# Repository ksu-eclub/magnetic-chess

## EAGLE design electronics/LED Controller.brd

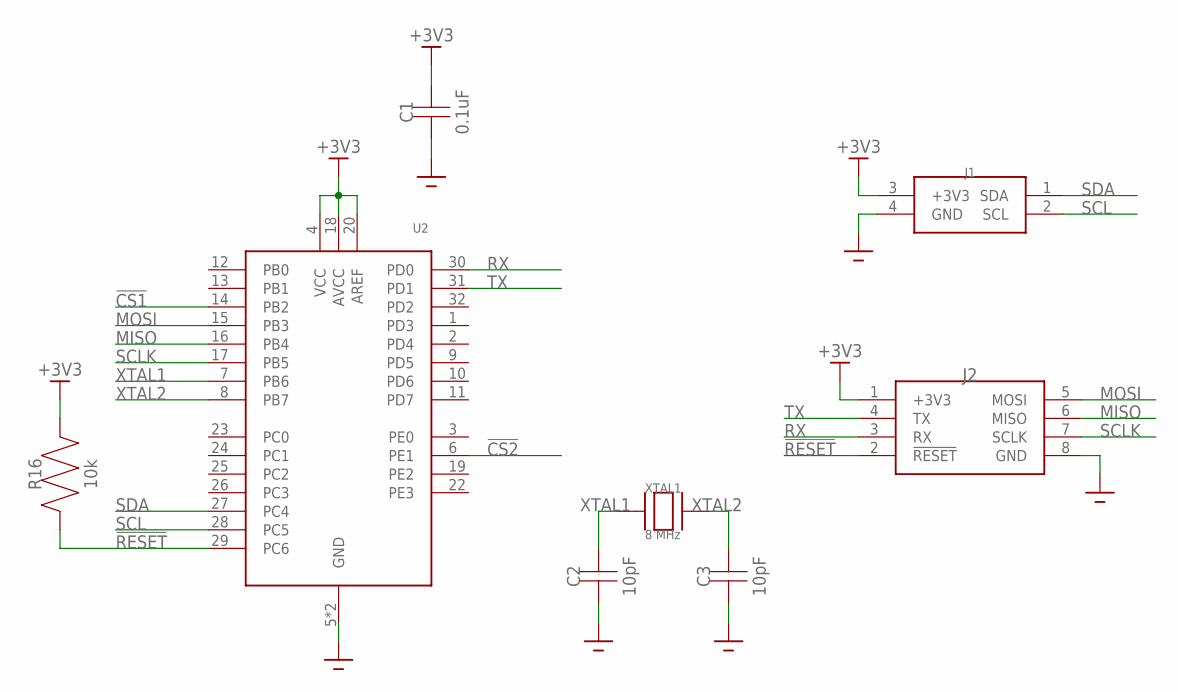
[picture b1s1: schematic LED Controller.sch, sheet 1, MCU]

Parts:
C1: 0.1uF; 0805
C2, C3: 10pF; 0805
J1: 1-770968-0
J2: DF1BZ-8DP-2.5DSA
R16: 10k; 0805
U2: ATMEGA328PB32-TQFP; ATMEGA328PB
XTAL1: 8 MHz; XRCGB

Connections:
!CS1: U2.14 (PB2); also elsewhere on the board
!CS2: U2.6 (PE1); also elsewhere on the board
!RESET: J2.2 (!RESET), R16.P$1, U2.29 (PC6)
+3V3: C1.P$2, J1.3 (+3V3), J2.1 (+3V3), R16.P$2, U2.4 (VCC), U2.18 (AVCC), U2.20 (AREF); also elsewhere on the board
GND: C1.P$1, C2.P$1, C3.P$1, J1.4 (GND), J2.8 (GND), U2.5 (GND), U2.21 (GND); also elsewhere on the board
MISO: J2.6 (MISO), U2.16 (PB4); also elsewhere on the board
MOSI: J2.5 (MOSI), U2.15 (PB3); also elsewhere on the board
RX: J2.3 (RX), U2.30 (PD0)
SCL: J1.2 (SCL), U2.28 (PC5)
SCLK: J2.7 (SCLK), U2.17 (PB5); also elsewhere on the board
SDA: J1.1 (SDA), U2.27 (PC4)
TX: J2.4 (TX), U2.31 (PD1)
XTAL1: C2.P$2, U2.7 (PB6), XTAL1.1, XTAL1.3
XTAL2: C3.P$2, U2.8 (PB7), XTAL1.2, XTAL1.4

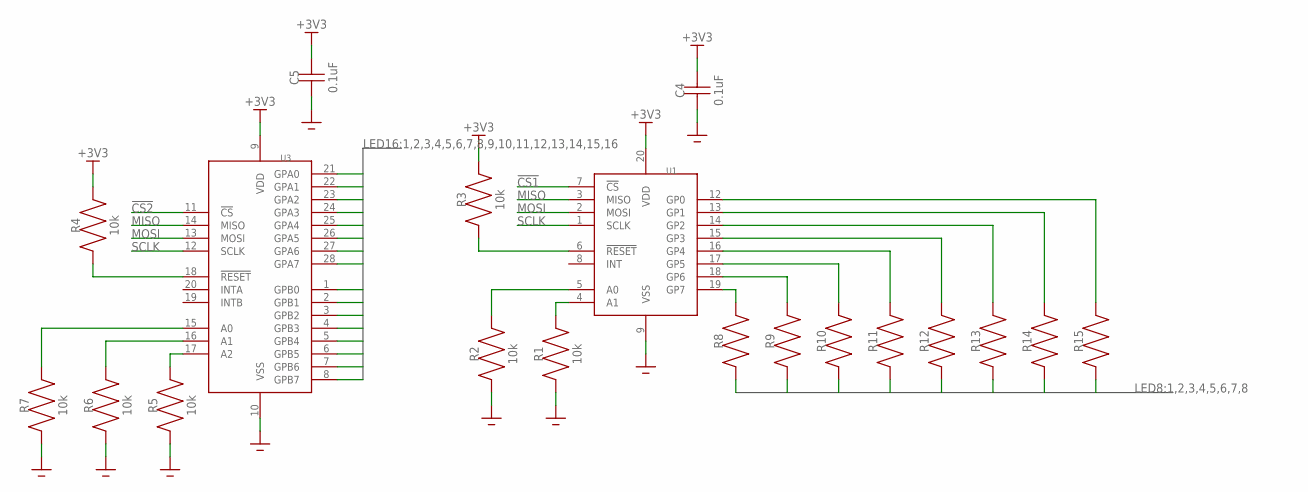
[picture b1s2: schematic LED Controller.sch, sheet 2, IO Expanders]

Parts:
C4, C5: 0.1uF; 0805
R1, R2, R3, R4, R5, R6, R7: 10k; 0805
R8, R9, R10, R11, R12, R13, R14, R15: RESISTOR0805; 0805
U1: MCP23S08-E/SO
U3: MCP23S17T-E/SO

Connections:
1: U3.21 (GPA0); also elsewhere on the board
2: U3.22 (GPA1); also elsewhere on the board
3: U3.23 (GPA2); also elsewhere on the board
4: U3.24 (GPA3); also elsewhere on the board
5: U3.25 (GPA4); also elsewhere on the board
6: U3.26 (GPA5); also elsewhere on the board
7: U3.27 (GPA6); also elsewhere on the board
8: U3.28 (GPA7); also elsewhere on the board
9: U3.1 (GPB0); also elsewhere on the board
10: U3.2 (GPB1); also elsewhere on the board
11: U3.3 (GPB2); also elsewhere on the board
12: U3.4 (GPB3); also elsewhere on the board
13: U3.5 (GPB4); also elsewhere on the board
14: U3.6 (GPB5); also elsewhere on the board
15: U3.7 (GPB6); also elsewhere on the board
16: U3.8 (GPB7); also elsewhere on the board
!CS1: U1.7 (!CS); also elsewhere on the board
!CS2: U3.11 (!CS); also elsewhere on the board
+3V3: C4.P$2, C5.P$2, R3.P$2, R4.P$2, U1.20 (VDD), U3.9 (VDD); also elsewhere on the board
A: R15.P$1; also elsewhere on the board
B: R14.P$1; also elsewhere on the board
C: R13.P$1; also elsewhere on the board
D: R12.P$1; also elsewhere on the board
E: R11.P$1; also elsewhere on the board
F: R10.P$1; also elsewhere on the board
G: R9.P$1; also elsewhere on the board
GND: C4.P$1, C5.P$1, R1.P$1, R2.P$1, R5.P$1, R6.P$1, R7.P$1, U1.9 (VSS), U3.10 (VSS); also elsewhere on the board
H: R8.P$1; also elsewhere on the board
MISO: U1.3 (MISO), U3.14 (MISO); also elsewhere on the board
MOSI: U1.2 (MOSI), U3.13 (MOSI); also elsewhere on the board
unnamed: R1.P$2, U1.4 (A1)
unnamed: R2.P$2, U1.5 (A0)
unnamed: R3.P$1, U1.6 (!RESET)
unnamed: R4.P$1, U3.18 (!RESET)
unnamed: R5.P$2, U3.17 (A2)
unnamed: R6.P$2, U3.16 (A1)
unnamed: R7.P$2, U3.15 (A0)
unnamed: R8.P$2, U1.19 (GP7)
unnamed: R9.P$2, U1.18 (GP6)
unnamed: R10.P$2, U1.17 (GP5)
unnamed: R11.P$2, U1.16 (GP4)
unnamed: R12.P$2, U1.15 (GP3)
unnamed: R13.P$2, U1.14 (GP2)
unnamed: R14.P$2, U1.13 (GP1)
unnamed: R15.P$2, U1.12 (GP0)
SCLK: U1.1 (SCLK), U3.12 (SCLK); also elsewhere on the board

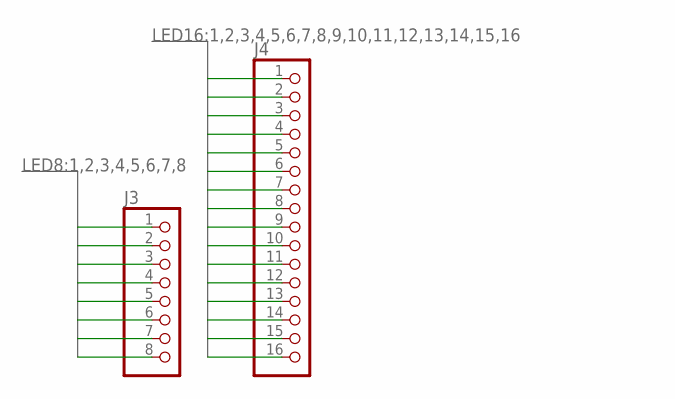
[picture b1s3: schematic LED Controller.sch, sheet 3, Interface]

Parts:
J3: LED8
J4: LED16

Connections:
1: J4.1; also elsewhere on the board
2: J4.2; also elsewhere on the board
3: J4.3; also elsewhere on the board
4: J4.4; also elsewhere on the board
5: J4.5; also elsewhere on the board
6: J4.6; also elsewhere on the board
7: J4.7; also elsewhere on the board
8: J4.8; also elsewhere on the board
9: J4.9; also elsewhere on the board
10: J4.10; also elsewhere on the board
11: J4.11; also elsewhere on the board
12: J4.12; also elsewhere on the board
13: J4.13; also elsewhere on the board
14: J4.14; also elsewhere on the board
15: J4.15; also elsewhere on the board
16: J4.16; also elsewhere on the board
A: J3.1; also elsewhere on the board
B: J3.2; also elsewhere on the board
C: J3.3; also elsewhere on the board
D: J3.4; also elsewhere on the board
E: J3.5; also elsewhere on the board
F: J3.6; also elsewhere on the board
G: J3.7; also elsewhere on the board
H: J3.8; also elsewhere on the board

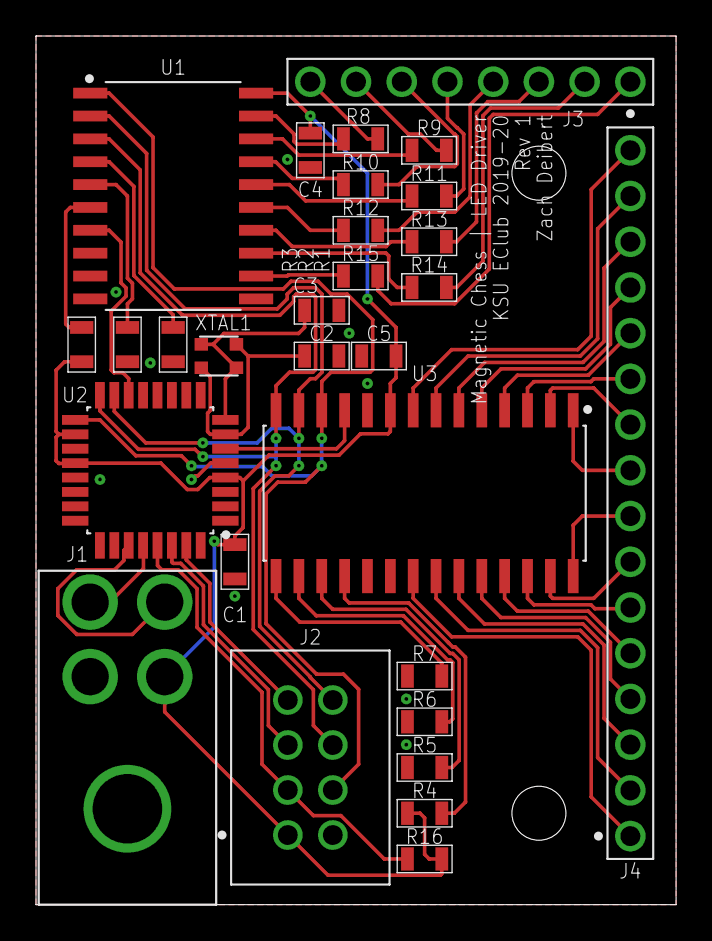
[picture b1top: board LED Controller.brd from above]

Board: 2 copper layers, 35.6 x 48.3 mm, 29 parts (0 on the bottom side), 53 nets.

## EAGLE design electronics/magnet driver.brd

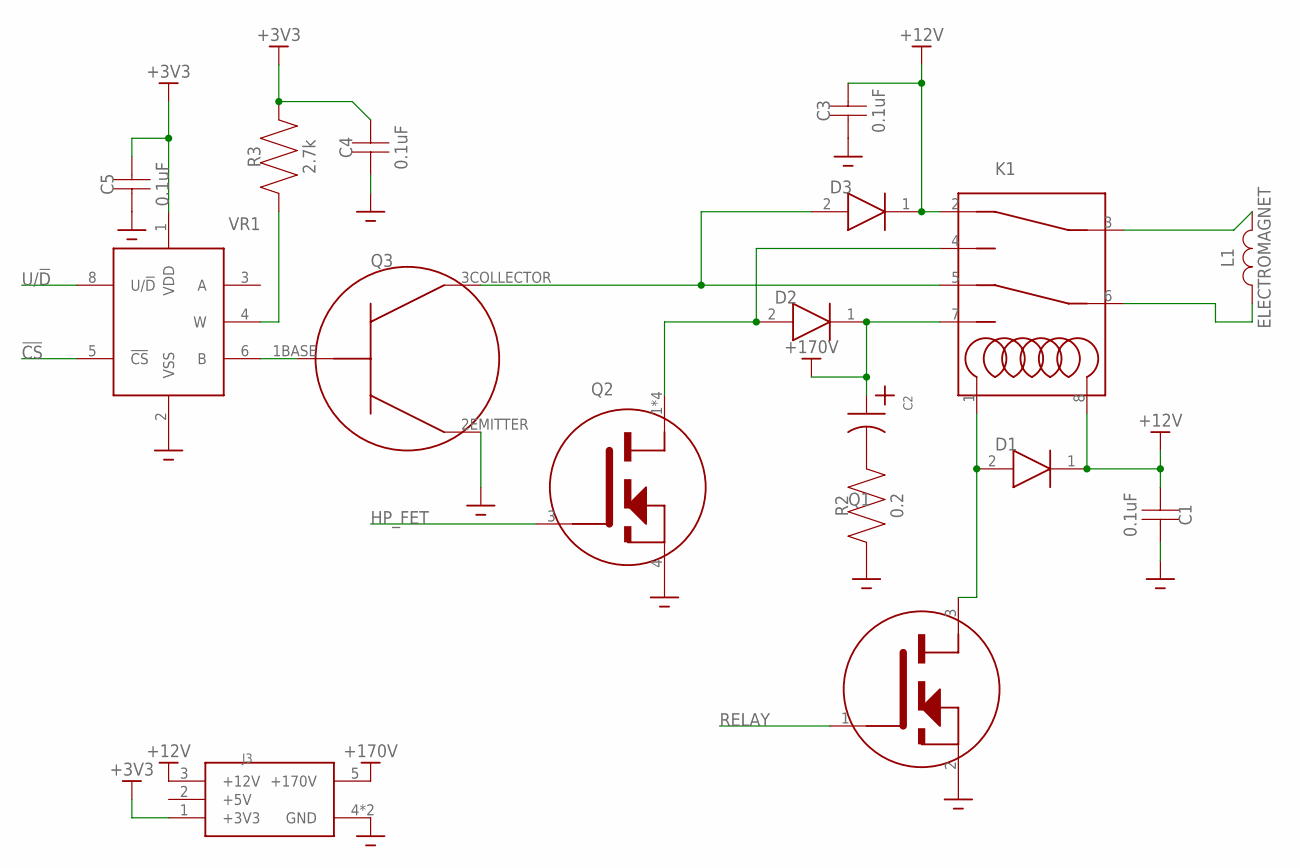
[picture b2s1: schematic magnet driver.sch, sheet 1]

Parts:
C1, C3, C4, C5: 0.1uF; 0805
C2: ESMQ351VSN102MA50S
D1, D2, D3: BAT54HT1GBAT54HT1G; SOD2512X110N
J3: 1-770969-0
K1: G2RL-2DC12
L1: ELECTROMAGNET
Q1: RK7002BMT116; SOT95P240X120-3N
Q2: DMN1019UVT-7DMN1019UVT-7; SOT95P280X100-6N
Q3: PMBT2222A,215PMBT2222A,215; SOT95P230X110-3N
R2: 0.2; 0805
R3: 2.7k; 0805
VR1: MCP4011-103E/MSMCP4011-103E/MS; SOP65P490X265-8N

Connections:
!CS: VR1.5 (!CS); also elsewhere on the board
+3V3: C4.P$2, C5.P$2, J3.1 (+3V3), R3.P$2, VR1.1 (VDD); also elsewhere on the board
+5V: J3.2 (+5V)
+12V: C1.P$1, C3.P$2, D1.1 (CATHODE(1)), D3.1 (CATHODE(1)), J3.3 (+12V), K1.2 (A1), K1.8 (COILOUT)
+170V: C2.+, D2.1 (CATHODE(1)), J3.5 (+170V), K1.7 (B2)
GND: C1.P$2, C3.P$1, C4.P$1, C5.P$1, J3.4 (GND), J3.6 (GND), Q1.2 (SOURCE(2)), Q2.4 (SOURCE(2)), Q3.2EMITTER (2E), R2.P$1, VR1.2 (VSS); also elsewhere on the board
HP_FET: Q2.3 (GATE(1)); also elsewhere on the board
unnamed: K1.3 (A), L1.-
unnamed: C2.-, R2.P$2
unnamed: D1.2 (ANODE(2)), K1.1 (COILIN), Q1.3 (DRAIN(3))
unnamed: K1.6 (B), L1.+
unnamed: Q3.1BASE (1B), VR1.6 (B)
unnamed: R3.P$1, VR1.4 (W)
unnamed: D3.2 (ANODE(2)), K1.5 (B1), Q3.3COLLECTOR (3C)
unnamed: D2.2 (ANODE(2)), K1.4 (A2), Q2.1 (DRAIN(3)), Q2.2 (DRAIN(3)), Q2.5 (DRAIN(3)), Q2.6 (DRAIN(3))
RELAY: Q1.1 (GATE(1)); also elsewhere on the board
U/!D: VR1.8 (U/!D); also elsewhere on the board

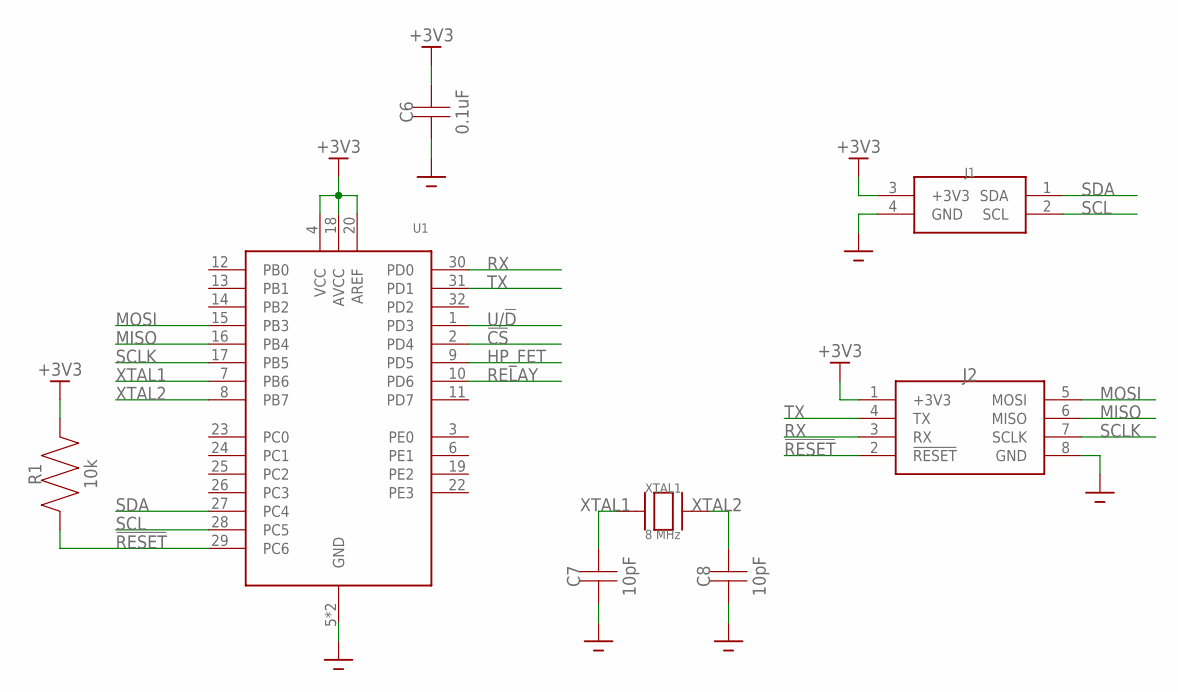
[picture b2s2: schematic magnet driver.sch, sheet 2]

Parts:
C6: 0.1uF; 0805
C7, C8: 10pF; 0805
J1: 1-770968-0
J2: DF1BZ-8DP-2.5DSA
R1: 10k; 0805
U1: ATMEGA328PB32-TQFP; ATMEGA328PB
XTAL1: 8 MHz; XRCGB

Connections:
!CS: U1.2 (PD4); also elsewhere on the board
!RESET: J2.2 (!RESET), R1.P$1, U1.29 (PC6)
+3V3: C6.P$2, J1.3 (+3V3), J2.1 (+3V3), R1.P$2, U1.4 (VCC), U1.18 (AVCC), U1.20 (AREF); also elsewhere on the board
GND: C6.P$1, C7.P$1, C8.P$1, J1.4 (GND), J2.8 (GND), U1.5 (GND), U1.21 (GND); also elsewhere on the board
HP_FET: U1.9 (PD5); also elsewhere on the board
MISO: J2.6 (MISO), U1.16 (PB4)
MOSI: J2.5 (MOSI), U1.15 (PB3)
RELAY: U1.10 (PD6); also elsewhere on the board
RX: J2.3 (RX), U1.30 (PD0)
SCL: J1.2 (SCL), U1.28 (PC5)
SCLK: J2.7 (SCLK), U1.17 (PB5)
SDA: J1.1 (SDA), U1.27 (PC4)
TX: J2.4 (TX), U1.31 (PD1)
U/!D: U1.1 (PD3); also elsewhere on the board
XTAL1: C7.P$2, U1.7 (PB6), XTAL1.1, XTAL1.3
XTAL2: C8.P$2, U1.8 (PB7), XTAL1.2, XTAL1.4

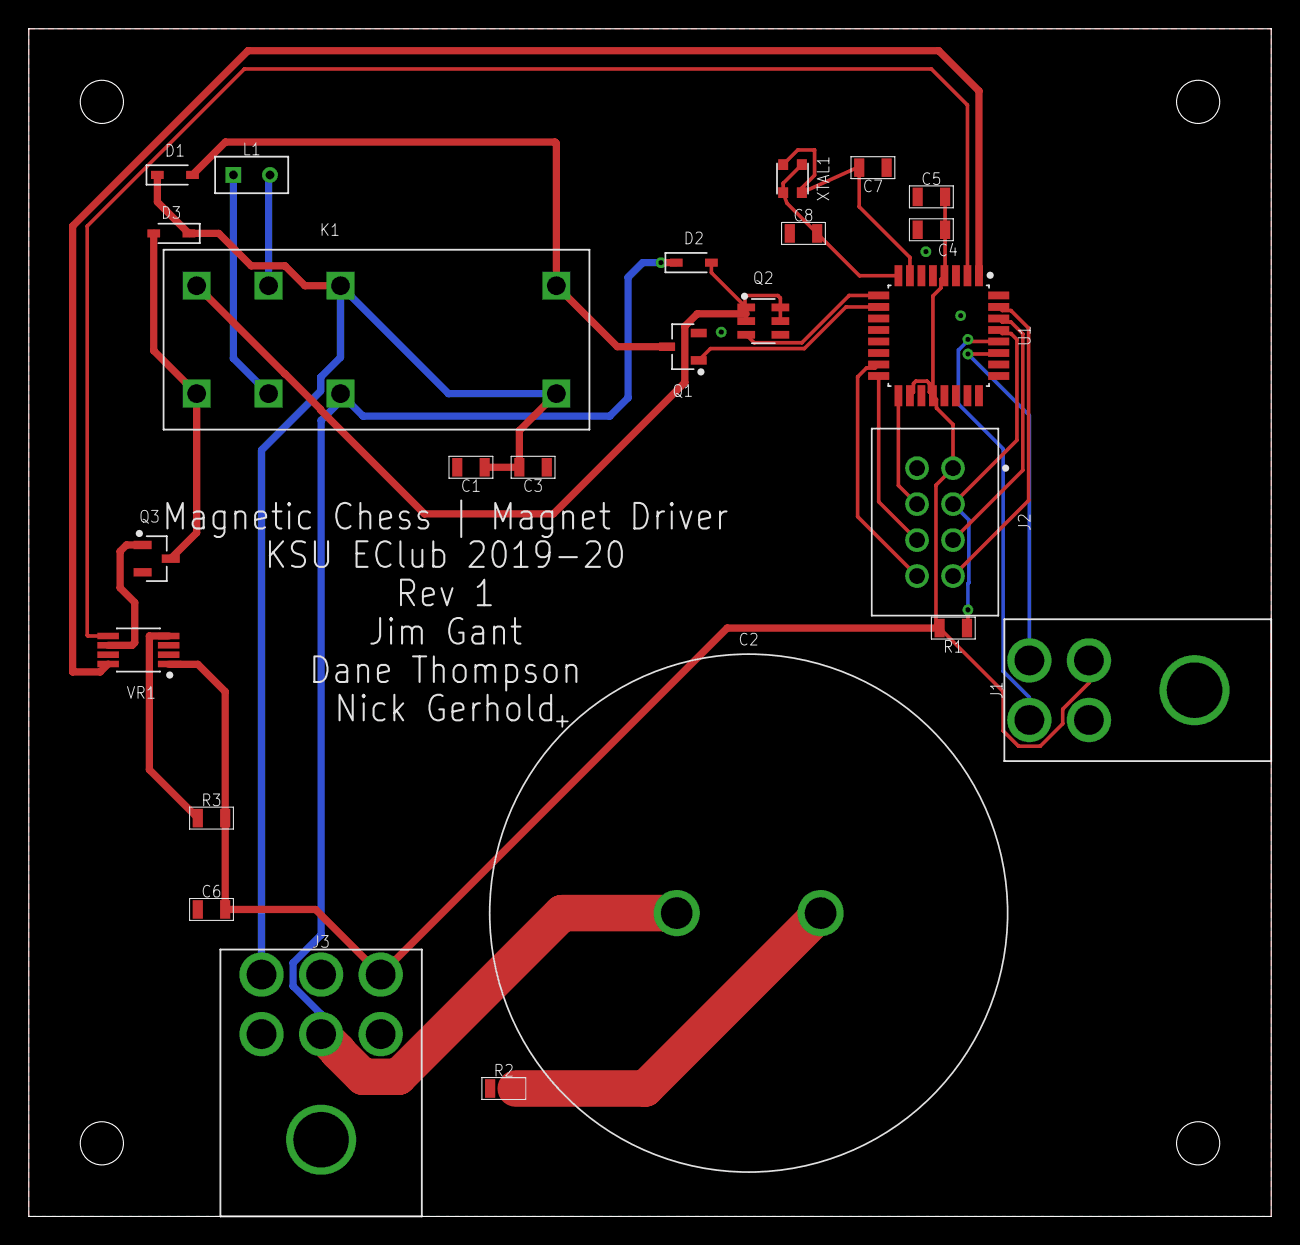
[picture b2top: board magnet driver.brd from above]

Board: 2 copper layers, 86.4 x 82.5 mm, 25 parts (0 on the bottom side), 26 nets.

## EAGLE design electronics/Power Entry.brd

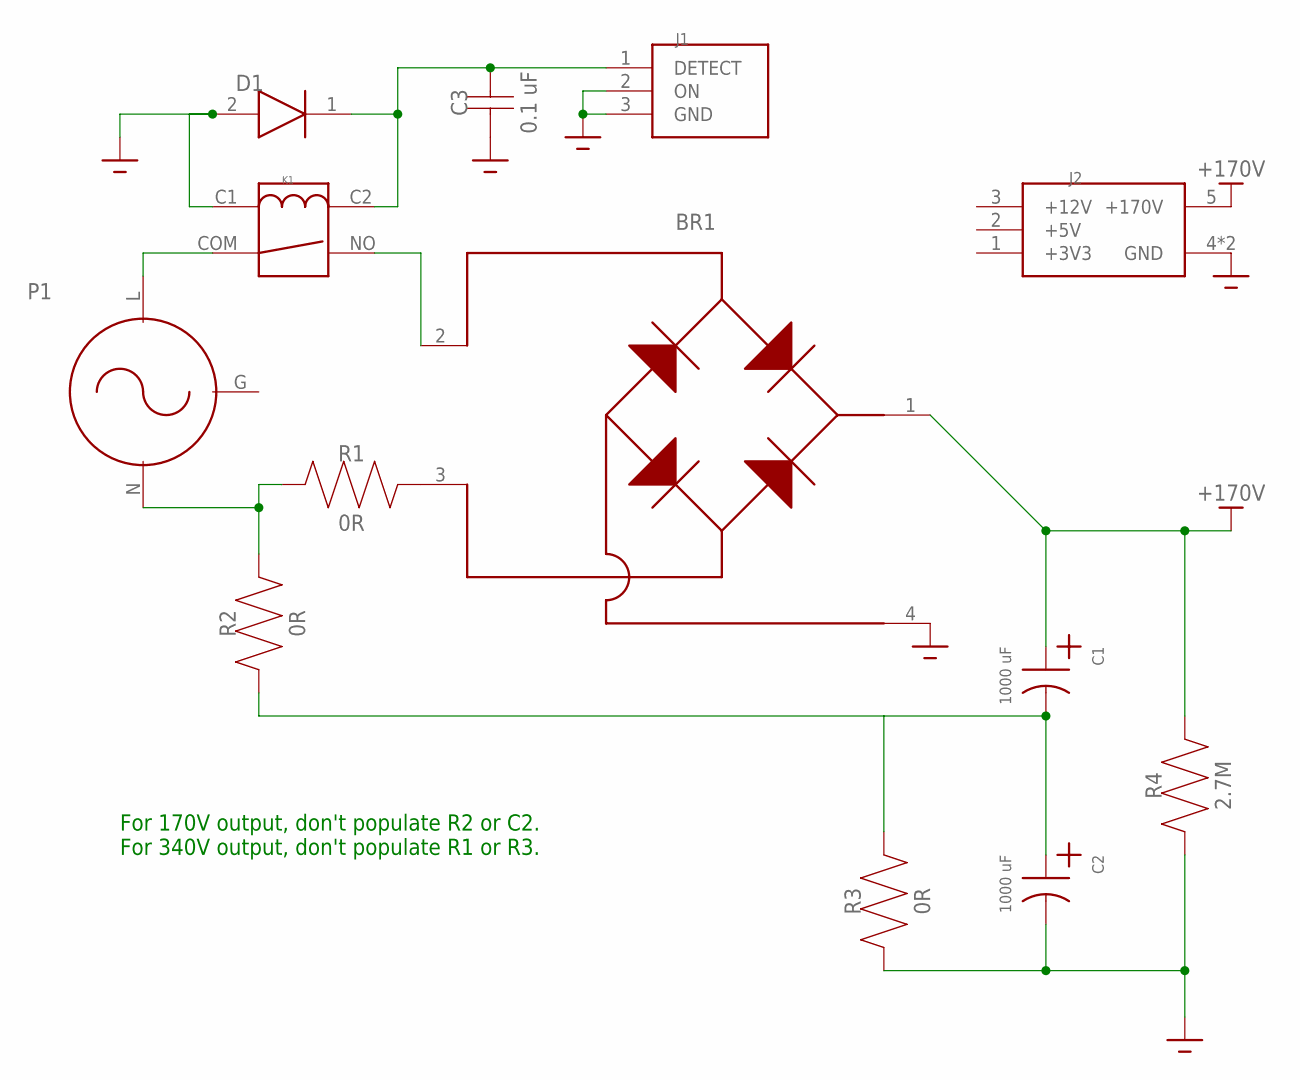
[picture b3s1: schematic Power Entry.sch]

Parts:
BR1: GBJ1004-BP
C1, C2: 1000 uF; ESMQ351VSN102MA50S
C3: 0.1 uF; 0805
D1: BAT54HT1GBAT54HT1G; SOD2512X110N
J1: 1-770967-0
J2: 1-770969-0
K1: ALQ3F12
P1: 703W-00/04
R1, R2, R3: 0R; 0805
R4: 2.7M; 0805

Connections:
+3V3: J2.1 (+3V3)
+5V: J2.2 (+5V)
+12V: J2.3 (+12V)
+170V: BR1.1 (POSITIVE_DC), C1.+, J2.5 (+170V), R4.P$2
GND: BR1.4 (NEGATIVE_DC), C2.-, C3.P$1, D1.2 (ANODE(2)), J1.2 (ON), J1.3 (GND), J2.4 (GND), J2.6 (GND), K1.C1, R3.P$1, R4.P$1
unnamed: BR1.3 (AC_IN2), R1.P$2
unnamed: P1.N (NEUTRAL), R1.P$1, R2.P$2
unnamed: C1.-, C2.+, R2.P$1, R3.P$2
unnamed: K1.COM (S1), P1.L (LIVE)
unnamed: BR1.2 (AC_IN1), K1.NO (S2)
unnamed: C3.P$2, D1.1 (CATHODE(1)), J1.1 (DETECT), K1.C2

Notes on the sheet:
For 170V output, don't populate R2 or C2. For 340V output, don't populate R1 or R3.

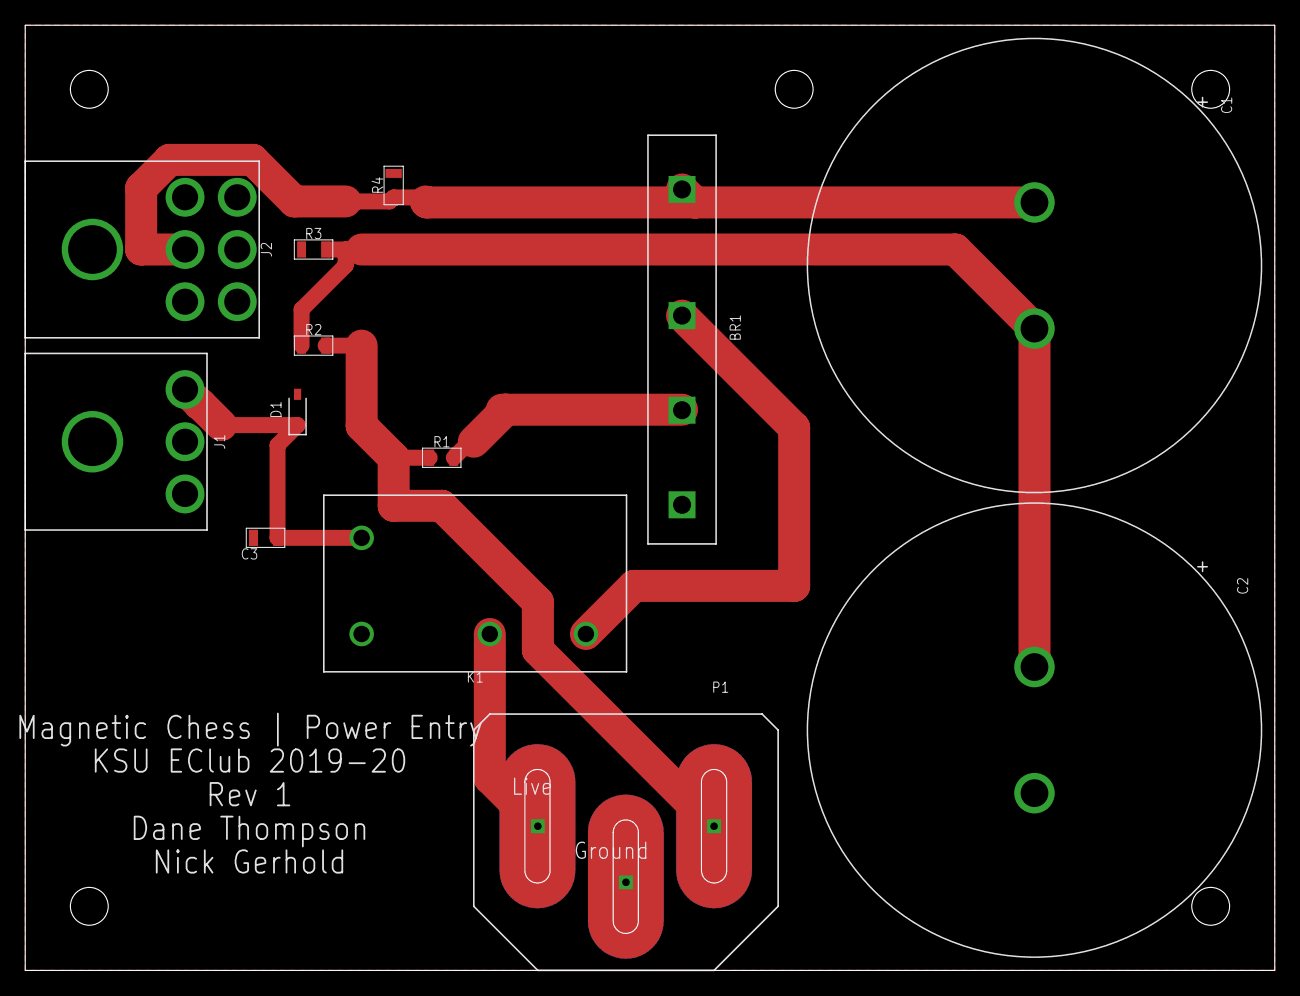
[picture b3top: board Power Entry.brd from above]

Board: 2 copper layers, 99.1 x 74.9 mm, 13 parts (0 on the bottom side), 8 nets.

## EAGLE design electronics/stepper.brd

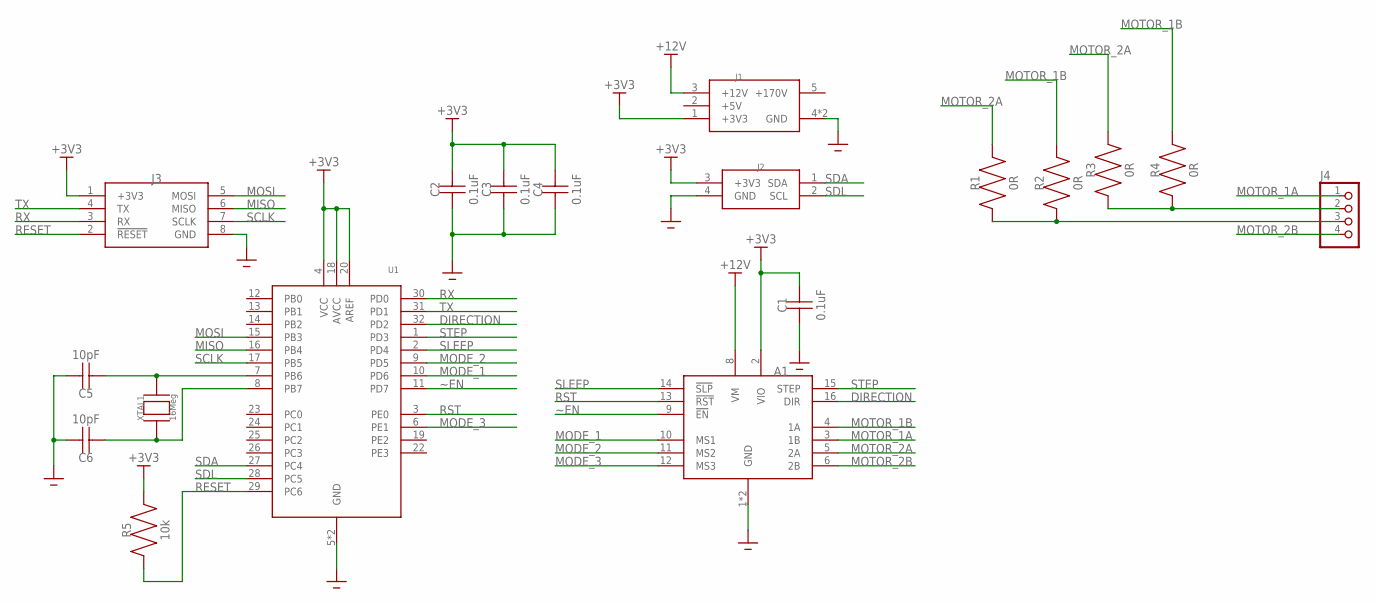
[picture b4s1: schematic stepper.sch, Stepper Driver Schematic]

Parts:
A1: STEPPER_DRIVER
C1, C2, C3, C4: 0.1uF; 0402
C5, C6: 10pF; 0402
J1: 1-770969-0
J2: 1-770968-0
J3: DF1BZ-8DP-2.5DSA
J4: S4B-XH-A
R1, R2, R3, R4: 0R; 0402
R5: 10k; 0402
U1: ATMEGA328PB32-TQFP; ATMEGA328PB
XTAL1: 16Meg; XRCGB

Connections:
+3V3: A1.2 (VIO), C1.2, C2.2, C3.2, C4.2, J1.1 (+3V3), J2.3 (+3V3), J3.1 (+3V3), R5.2, U1.4 (VCC), U1.18 (AVCC), U1.20 (AREF)
+5V: J1.2 (+5V)
+12V: A1.8 (VM), J1.3 (+12V)
+170V: J1.5 (+170V)
DIRECTION: A1.16 (DIR), U1.32 (PD2)
GND: A1.1 (GND), A1.7 (GND), C1.1, C2.1, C3.1, C4.1, C5.2, C6.2, J1.4 (GND), J1.6 (GND), J2.4 (GND), J3.8 (GND), U1.5 (GND), U1.21 (GND)
MISO: J3.6 (MISO), U1.16 (PB4)
MODE_1: A1.10 (MS1), U1.10 (PD6)
MODE_2: A1.11 (MS2), U1.9 (PD5)
MODE_3: A1.12 (MS3), U1.6 (PE1)
MOSI: J3.5 (MOSI), U1.15 (PB3)
MOTOR_1A: A1.3 (1B), J4.1
MOTOR_1B: A1.4 (1A), R2.2, R4.2
MOTOR_2A: A1.5 (2A), R1.2, R3.2
MOTOR_2B: A1.6 (2B), J4.4
unnamed: C5.1, U1.7 (PB6), XTAL1.2, XTAL1.4
unnamed: C6.1, U1.8 (PB7), XTAL1.1, XTAL1.3
unnamed: J4.2, R3.1, R4.1
unnamed: J4.3, R1.1, R2.1
RESET: J3.2 (!RESET), R5.1, U1.29 (PC6)
RST: A1.13 (!RST), U1.3 (PE0)
RX: J3.3 (RX), U1.30 (PD0)
SCLK: J3.7 (SCLK), U1.17 (PB5)
SDA: J2.1 (SDA), U1.27 (PC4)
SDL: J2.2 (SCL), U1.28 (PC5)
SLEEP: A1.14 (!SLP), U1.2 (PD4)
STEP: A1.15 (STEP), U1.1 (PD3)
TX: J3.4 (TX), U1.31 (PD1)
~EN: A1.9 (!EN), U1.11 (PD7)

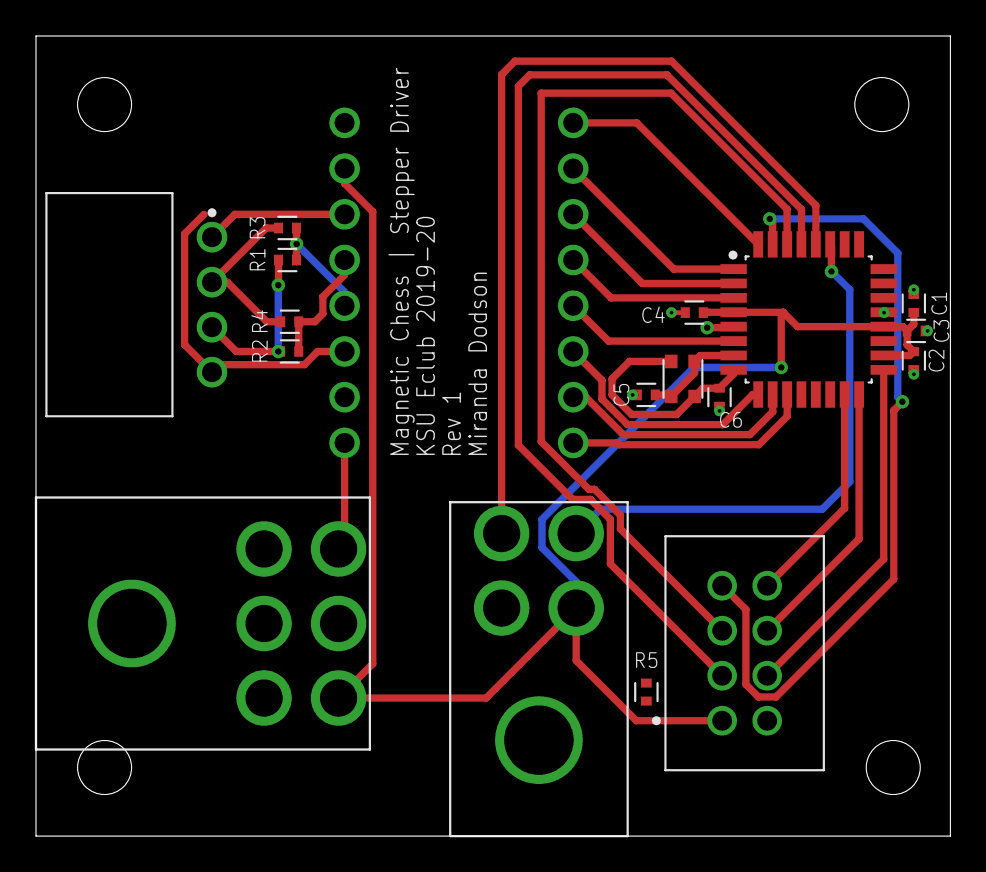
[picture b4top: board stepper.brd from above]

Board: 2 copper layers, 50.8 x 44.5 mm, 18 parts (1 on the bottom side), 27 nets.

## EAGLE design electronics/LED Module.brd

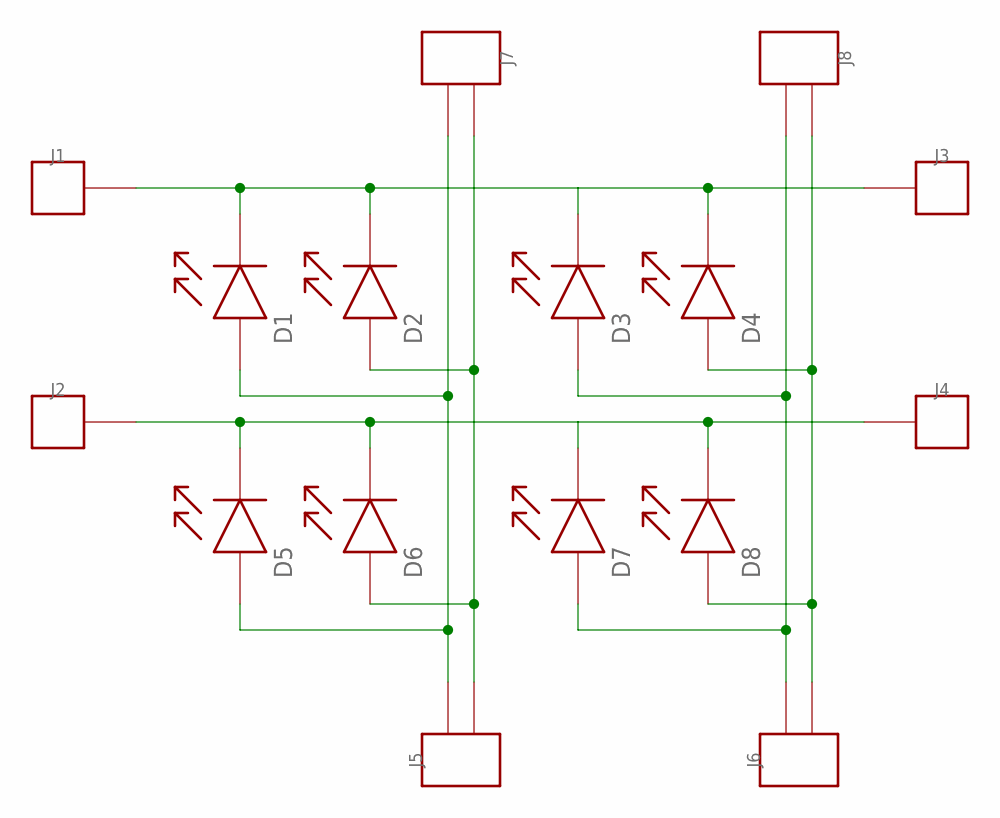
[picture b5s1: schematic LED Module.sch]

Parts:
D1, D2, D3, D4, D5, D6, D7, D8: LED; 0805-POL
J1, J2, J3, J4: LED_JUMPER_1
J5, J6, J7, J8: LED_JUMPER_2

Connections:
unnamed: D1.+ (K), D2.+ (K), D3.+ (K), D4.+ (K), J1.1, J3.1
unnamed: D1.COM (A), D5.COM (A), J5.1, J7.2
unnamed: D2.COM (A), D6.COM (A), J5.2, J7.1
unnamed: D5.+ (K), D6.+ (K), D7.+ (K), D8.+ (K), J2.1, J4.1
unnamed: D3.COM (A), D7.COM (A), J6.1, J8.2
unnamed: D4.COM (A), D8.COM (A), J6.2, J8.1

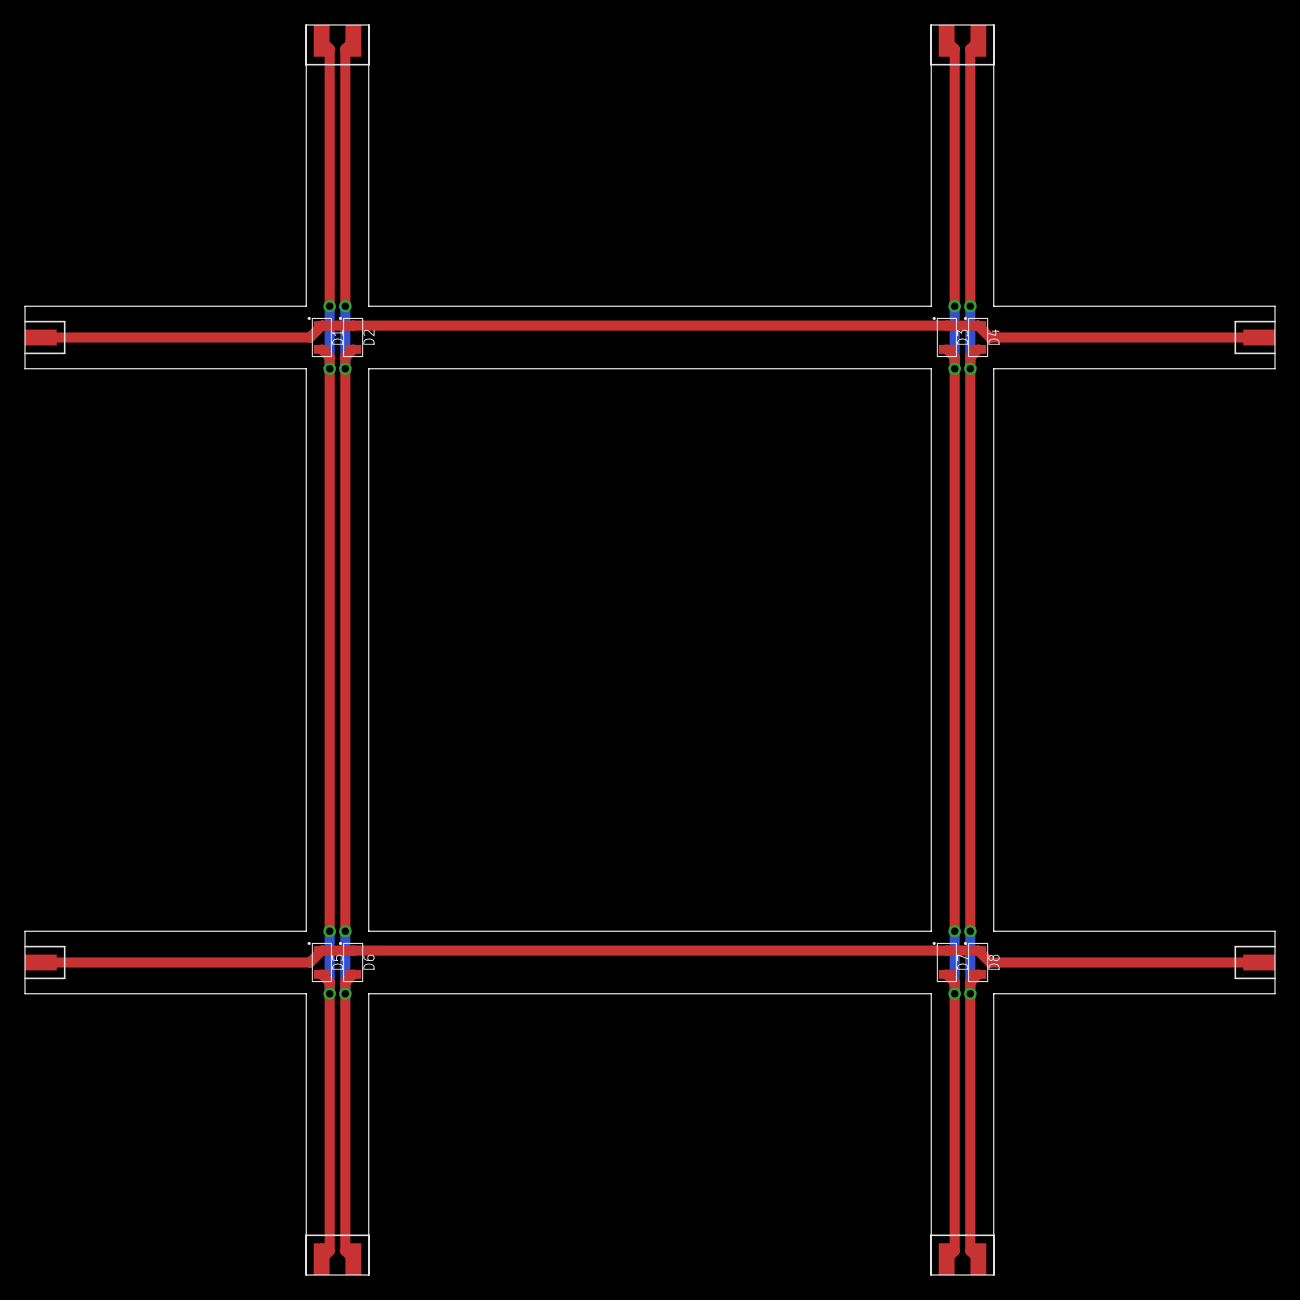
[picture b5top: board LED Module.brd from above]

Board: 2 copper layers, 100.0 x 100.0 mm, 16 parts (0 on the bottom side), 6 nets.

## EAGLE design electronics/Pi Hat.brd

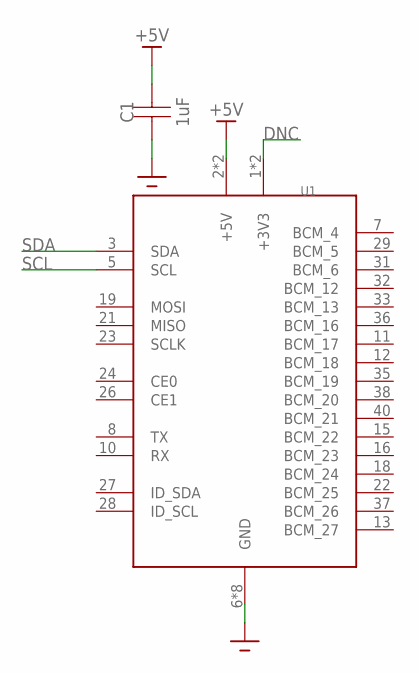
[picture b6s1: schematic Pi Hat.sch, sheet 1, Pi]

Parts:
C1: 1uF; 0805
U1: RPI

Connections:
+5V: C1.P$2, U1.2 (+5V), U1.4 (+5V); also elsewhere on the board
DNC: U1.1 (+3V3), U1.17 (+3V3)
GND: C1.P$1, U1.6 (GND), U1.9 (GND), U1.14 (GND), U1.20 (GND), U1.25 (GND), U1.30 (GND), U1.34 (GND), U1.39 (GND); also elsewhere on the board
SCL: U1.5 (SCL); also elsewhere on the board
SDA: U1.3 (SDA); also elsewhere on the board

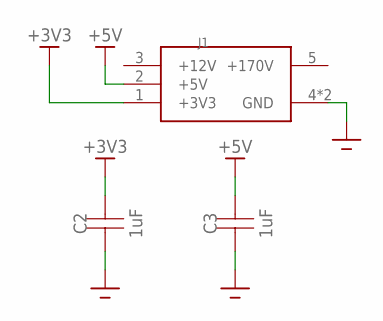
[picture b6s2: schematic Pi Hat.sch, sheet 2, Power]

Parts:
C2, C3: 1uF; 0805
J1: 1-770969-0

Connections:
+3V3: C2.P$2, J1.1 (+3V3); also elsewhere on the board
+5V: C3.P$2, J1.2 (+5V); also elsewhere on the board
+12V: J1.3 (+12V)
+170V: J1.5 (+170V)
GND: C2.P$1, C3.P$1, J1.4 (GND), J1.6 (GND); also elsewhere on the board

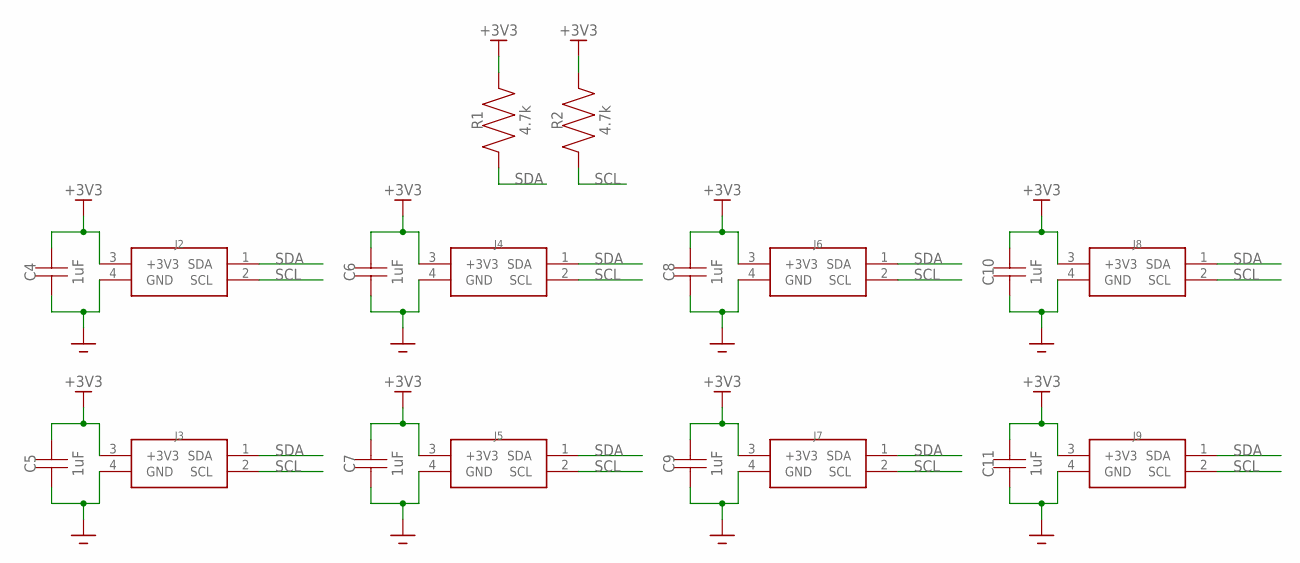
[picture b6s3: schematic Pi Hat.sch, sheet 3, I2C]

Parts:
C4, C5, C6, C7, C8, C9, C10, C11: 1uF; 0805
J2, J3, J4, J5, J6, J7, J8, J9: 1-770968-0
R1, R2: 4.7k; 0805

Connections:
+3V3: C4.P$2, C5.P$2, C6.P$2, C7.P$2, C8.P$2, C9.P$2, C10.P$2, C11.P$2, J2.3 (+3V3), J3.3 (+3V3), J4.3 (+3V3), J5.3 (+3V3), J6.3 (+3V3), J7.3 (+3V3), J8.3 (+3V3), J9.3 (+3V3), R1.P$2, R2.P$2; also elsewhere on the board
GND: C4.P$1, C5.P$1, C6.P$1, C7.P$1, C8.P$1, C9.P$1, C10.P$1, C11.P$1, J2.4 (GND), J3.4 (GND), J4.4 (GND), J5.4 (GND), J6.4 (GND), J7.4 (GND), J8.4 (GND), J9.4 (GND); also elsewhere on the board
SCL: J2.2 (SCL), J3.2 (SCL), J4.2 (SCL), J5.2 (SCL), J6.2 (SCL), J7.2 (SCL), J8.2 (SCL), J9.2 (SCL), R2.P$1; also elsewhere on the board
SDA: J2.1 (SDA), J3.1 (SDA), J4.1 (SDA), J5.1 (SDA), J6.1 (SDA), J7.1 (SDA), J8.1 (SDA), J9.1 (SDA), R1.P$1; also elsewhere on the board
